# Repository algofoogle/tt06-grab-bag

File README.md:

# Anton's TT06 grab bag

This is a simple analog/mixed-signal project, created from the [TT06 analog template repo](https://github.com/TinyTapeout/tt06-analog-template).

I was invited to participate in the first round of Matt Venn's Zero to ASIC **Analog Course** beta, and this was the design I ultimately submitted to TT06.

It implements:
*   A digital block that generates a few basic 24b-colour (RGB888) VGA test patterns.
*   Analog RGB outputs (running digital block VGA outputs through 3x 8-bit R2R DACs).
*   An extra 4-bit R2R DAC.
*   A bog-standard CMOS inverter. That was my very first custom layout attempt.

**For much more information, [read the full documentation](docs/info.md)**

See [`pcb/`](./pcb/) for PCBs I've been working on related to this.

# What is Tiny Tapeout?

Tiny Tapeout is an educational project that aims to make it easier and cheaper than ever to get your digital designs manufactured on a real chip.

To learn more and get started, visit https://tinytapeout.com.

# Analog projects

For specifications and instructions, see the [analog specs page](https://tinytapeout.com/specs/analog/).

If you have any questions, please join the [Tiny Tapeout Discord](https://tinytapeout.com/discord) and ask in the `#analog` channel.

# Resources

- [FAQ](https://tinytapeout.com/faq/)
- [Digital design lessons](https://tinytapeout.com/digital_design/)
- [Learn how semiconductors work](https://tinytapeout.com/siliwiz/)
- [Join the community](https://tinytapeout.com/discord)

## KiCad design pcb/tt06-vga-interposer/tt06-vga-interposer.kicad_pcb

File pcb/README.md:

# PCB design files for TT06 Grab Bag

*   [`tt06-vga-opamp/`](./tt06-vga-opamp/) is my original prototyping board that I made for testing tt06-grab-bag. I was originally working on it [here](https://github.com/algofoogle/sandpit/tree/master/opamp/tt06-vga-opamp) (private repo).
*   [`tt06-vga-interposer/`](./tt06-vga-interposer/) is a board I'm working on that sits between the TT06 chip carrier board and the TT06 demo board. It taps the analog signals relevant to this design and buffers them with an OPA3355, and includes a VGA socket.

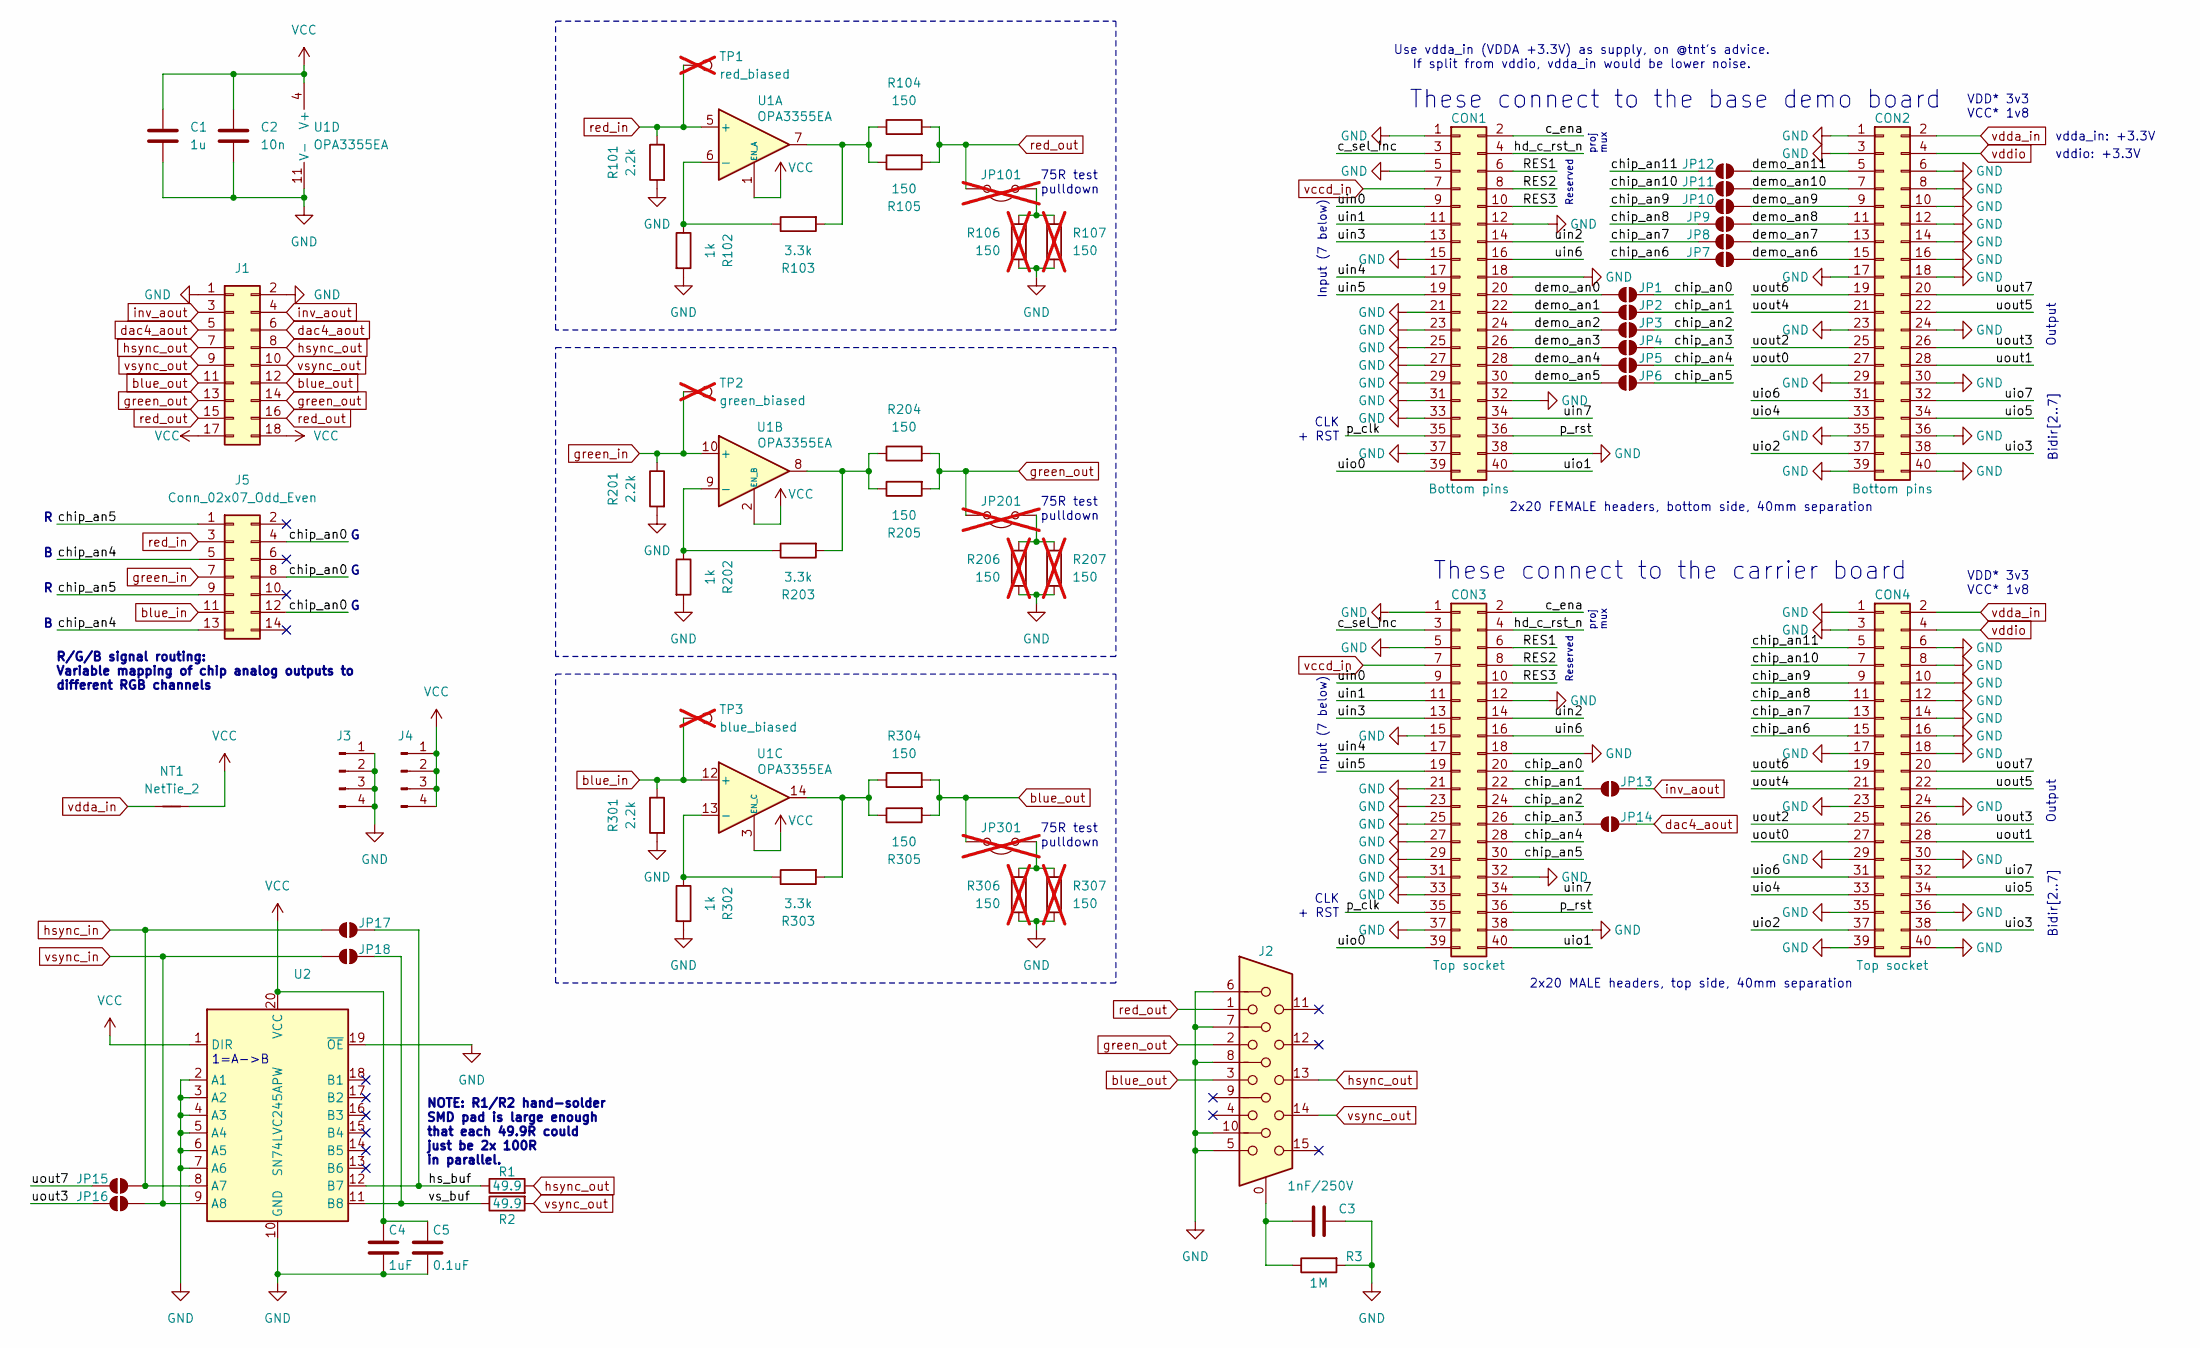
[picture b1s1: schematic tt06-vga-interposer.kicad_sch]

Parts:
C1: 1u; SMD_Passive_HandSolder_0603_to_1210
C2: 10n; SMD_Passive_HandSolder_0603_to_1210
C3: 1nF/250V; SMD_Passive_HandSolder_0603_to_1210
C4: 1uF; SMD_Passive_HandSolder_0603_to_1210
C5: 0.1uF; SMD_Passive_HandSolder_0603_to_1210
CON1, CON2: Bottom pins; PinSocket_2x20_P2.54mm_Vertical; MPN NPTC202KFMS-RC; DigikeyPN S5690-ND
CON3, CON4: Top socket; PinHeader_2x20_P2.54mm_Vertical; MPN NPTC202KFMS-RC; DigikeyPN S5690-ND
J1: Conn_02x09_Odd_Even; PinHeader_2x09_P2.54mm_Vertical
J2: DE15_Receptacle_HighDensity_MountingHoles; DSUB-15-HD_F_Horz_P2.29x2.54mm_EPO3.03mm_MO4.94mm_STRONG
J3, J4: Conn_01x04_Pin; PinHeader_1x04_P2.54mm_Vertical
J5: Conn_02x07_Odd_Even; PinHeader_2x07_P2.54mm_Horizontal
JP1, JP2, JP3, JP4, JP5, JP6, JP7, JP8, JP9, JP10, JP11, JP12, JP13, JP14, JP15, JP16, JP17, JP18: SolderJumper_2_Open; SolderJumper-2_tiny_nomask
JP101, JP201, JP301: Jumper_2_Open; PinHeader_2x01_P2.54mm_Vertical; not fitted
NT1: NetTie_2; NetTie-2_SMD_Pad0.5mm
R1, R2: 49.9; SMD_Passive_HandSolder_0603_to_1210
R3: 1M; SMD_Passive_HandSolder_0603_to_1210
R101, R201, R301: 2.2k; SMD_Passive_HandSolder_0603_to_1210
R102, R202, R302: 1k; SMD_Passive_HandSolder_0603_to_1210
R103, R203, R303: 3.3k; SMD_Passive_HandSolder_0603_to_1210
R104, R105, R204, R205, R304, R305: 150; SMD_Passive_HandSolder_0603_to_1210
R106, R107, R206, R207, R306, R307: 150; SMD_Passive_HandSolder_0603_to_1210; not fitted
TP1: red_biased; PinHeader_1x01_P2.54mm_Vertical; not fitted
TP2: green_biased; PinHeader_1x01_P2.54mm_Vertical; not fitted
TP3: blue_biased; PinHeader_1x01_P2.54mm_Vertical; not fitted
U1: OPA3355EA; TSSOP-14_4.4x5mm_P0.65mm_HandSolder
U2: SN74LVC245APW; TSSOP-20_4.4x6.5mm_P0.65mm_HandSolder

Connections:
/RES1: CON1.6, CON3.6
/RES2: CON1.8, CON3.8
/RES3: CON1.10, CON3.10
/c_ena: CON1.2, CON3.2
/c_sel_inc: CON1.3, CON3.3
/chip_an0: CON3.20, J5.4, J5.8, J5.12, JP1.2 (B)
/chip_an1: CON3.22, JP2.2 (B), JP13.1 (A)
/chip_an2: CON3.24, JP3.2 (B)
/chip_an3: CON3.26, JP4.2 (B), JP14.1 (A)
/chip_an4: CON3.28, J5.5, J5.13, JP5.2 (B)
/chip_an5: CON3.30, J5.1, J5.9, JP6.2 (B)
/chip_an6: CON4.15, JP7.2 (B)
/chip_an7: CON4.13, JP8.2 (B)
/chip_an8: CON4.11, JP9.2 (B)
/chip_an9: CON4.9, JP10.2 (B)
/chip_an10: CON4.7, JP11.2 (B)
/chip_an11: CON4.5, JP12.2 (B)
/demo_an0: CON1.20, JP1.1 (A)
/demo_an1: CON1.22, JP2.1 (A)
/demo_an2: CON1.24, JP3.1 (A)
/demo_an3: CON1.26, JP4.1 (A)
/demo_an4: CON1.28, JP5.1 (A)
/demo_an5: CON1.30, JP6.1 (A)
/demo_an6: CON2.15, JP7.1 (A)
/demo_an7: CON2.13, JP8.1 (A)
/demo_an8: CON2.11, JP9.1 (A)
/demo_an9: CON2.9, JP10.1 (A)
/demo_an10: CON2.7, JP11.1 (A)
/demo_an11: CON2.5, JP12.1 (A)
/hd_c_rst_n: CON1.4, CON3.4
/hs_buf: JP17.2 (B), R1.1, U2.12 (B7)
/p_clk: CON1.35, CON3.35
/p_rst: CON1.36, CON3.36
/uin0: CON1.9, CON3.9
/uin1: CON1.11, CON3.11
/uin2: CON1.14, CON3.14
/uin3: CON1.13, CON3.13
/uin4: CON1.17, CON3.17
/uin5: CON1.19, CON3.19
/uin6: CON1.16, CON3.16
/uin7: CON1.34, CON3.34
/uio0: CON1.39, CON3.39
/uio1: CON1.40, CON3.40
/uio2: CON2.37, CON4.37
/uio3: CON2.38, CON4.38
/uio4: CON2.33, CON4.33
/uio5: CON2.34, CON4.34
/uio6: CON2.31, CON4.31
/uio7: CON2.32, CON4.32
/uout0: CON2.27, CON4.27
/uout1: CON2.28, CON4.28
/uout2: CON2.25, CON4.25
/uout3: CON2.26, CON4.26, JP16.2 (B)
/uout4: CON2.21, CON4.21
/uout5: CON2.22, CON4.22
/uout6: CON2.19, CON4.19
/uout7: CON2.20, CON4.20, JP15.2 (B)
/vs_buf: JP18.2 (B), R2.1, U2.11 (B8)
GND: C1.2, C2.2, C3.2, C4.2, C5.2, CON1.1, CON1.5, CON1.12, CON1.15, CON1.18, CON1.21, CON1.23, CON1.25, CON1.27, CON1.29, CON1.31, CON1.32, CON1.33, CON1.37, CON1.38, CON2.1, CON2.3, CON2.6, CON2.8, CON2.10, CON2.12, CON2.14, CON2.16, CON2.17, CON2.18, CON2.23, CON2.24, CON2.29, CON2.30, CON2.35, CON2.36, CON2.39, CON2.40, CON3.1, CON3.5, CON3.12, CON3.15, CON3.18, CON3.21, CON3.23, CON3.25, CON3.27, CON3.29, CON3.31, CON3.32, CON3.33, CON3.37, CON3.38, CON4.1, CON4.3, CON4.6, CON4.8, CON4.10, CON4.12, CON4.14, CON4.16, CON4.17, CON4.18, CON4.23, CON4.24, CON4.29, CON4.30, CON4.35, CON4.36, CON4.39, CON4.40, J1.1, J1.2, J2.5, J2.6, J2.7, J2.8, J2.10, J3.1, J3.2, J3.3, J3.4, R3.2, R101.2, R102.2, R106.1, R107.1, R201.2, R202.2, R206.1, R207.1, R301.2, R302.2, R306.1, R307.1, U1.11 (V-), U2.2 (A1), U2.3 (A2), U2.4 (A3), U2.5 (A4), U2.6 (A5), U2.7 (A6), U2.10 (GND), U2.19 (~OE)
unnamed: C3.1, J2.0, R3.1
unnamed: JP101.2 (B), R106.2, R107.2
unnamed: JP201.2 (B), R206.2, R207.2
unnamed: JP301.2 (B), R306.2, R307.2
unnamed: R103.2, R104.1, R105.1, U1.7
unnamed: R203.2, R204.1, R205.1, U1.8
unnamed: R303.2, R304.1, R305.1, U1.14
unnamed: R102.1, R103.1, U1.6 (-)
unnamed: R202.1, R203.1, U1.9 (-)
unnamed: R302.1, R303.1, U1.13 (-)
VCC: C1.1, C2.1, C4.1, C5.1, J1.17, J1.18, J4.1, J4.2, J4.3, J4.4, NT1.1, U1.1 (EN_A), U1.2 (EN_B), U1.3 (EN_C), U1.4 (V+), U2.1 (DIR), U2.20 (VCC)
blue_in: J5.11, R301.1, TP3.1, U1.12 (+)
blue_out: J1.11, J1.12, J2.3, JP301.1 (A), R304.2, R305.2
dac4_aout: J1.5, J1.6, JP14.2 (B)
green_in: J5.7, R201.1, TP2.1, U1.10 (+)
green_out: J1.13, J1.14, J2.2, JP201.1 (A), R204.2, R205.2
hsync_in: JP15.1 (A), JP17.1 (A), U2.8 (A7)
hsync_out: J1.7, J1.8, J2.13, R1.2
inv_aout: J1.3, J1.4, JP13.2 (B)
red_in: J5.3, R101.1, TP1.1, U1.5 (+)
red_out: J1.15, J1.16, J2.1, JP101.1 (A), R104.2, R105.2
vccd_in: CON1.7, CON3.7
vdda_in: CON2.2, CON4.2, NT1.2
vddio: CON2.4, CON4.4
vsync_in: JP16.1 (A), JP18.1 (A), U2.9 (A8)
vsync_out: J1.9, J1.10, J2.14, R2.2

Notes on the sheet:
Output
proj mux
Use vdda_in (VDDA +3.3V) as supply, on @tnt's advice. If split from vddio, vdda_in would be lower noise.
VDD* 3v3 VCC* 1v8
vdda_in: +3.3V
Reserved
75R test pulldown
These connect to the carrier board
2x20 FEMALE headers, bottom side, 40mm separation
Input (7 below)
2x20 MALE headers, top side, 40mm separation
vddio: +3.3V
R/G/B signal routing: Variable mapping of chip analog outputs to different RGB channels
NOTE: R1/R2 hand-solder SMD pad is large enough that each 49.9R could just be 2x 100R in parallel.
Bidir[2..7]
These connect to the base demo board
1=A->B
CLK + RST

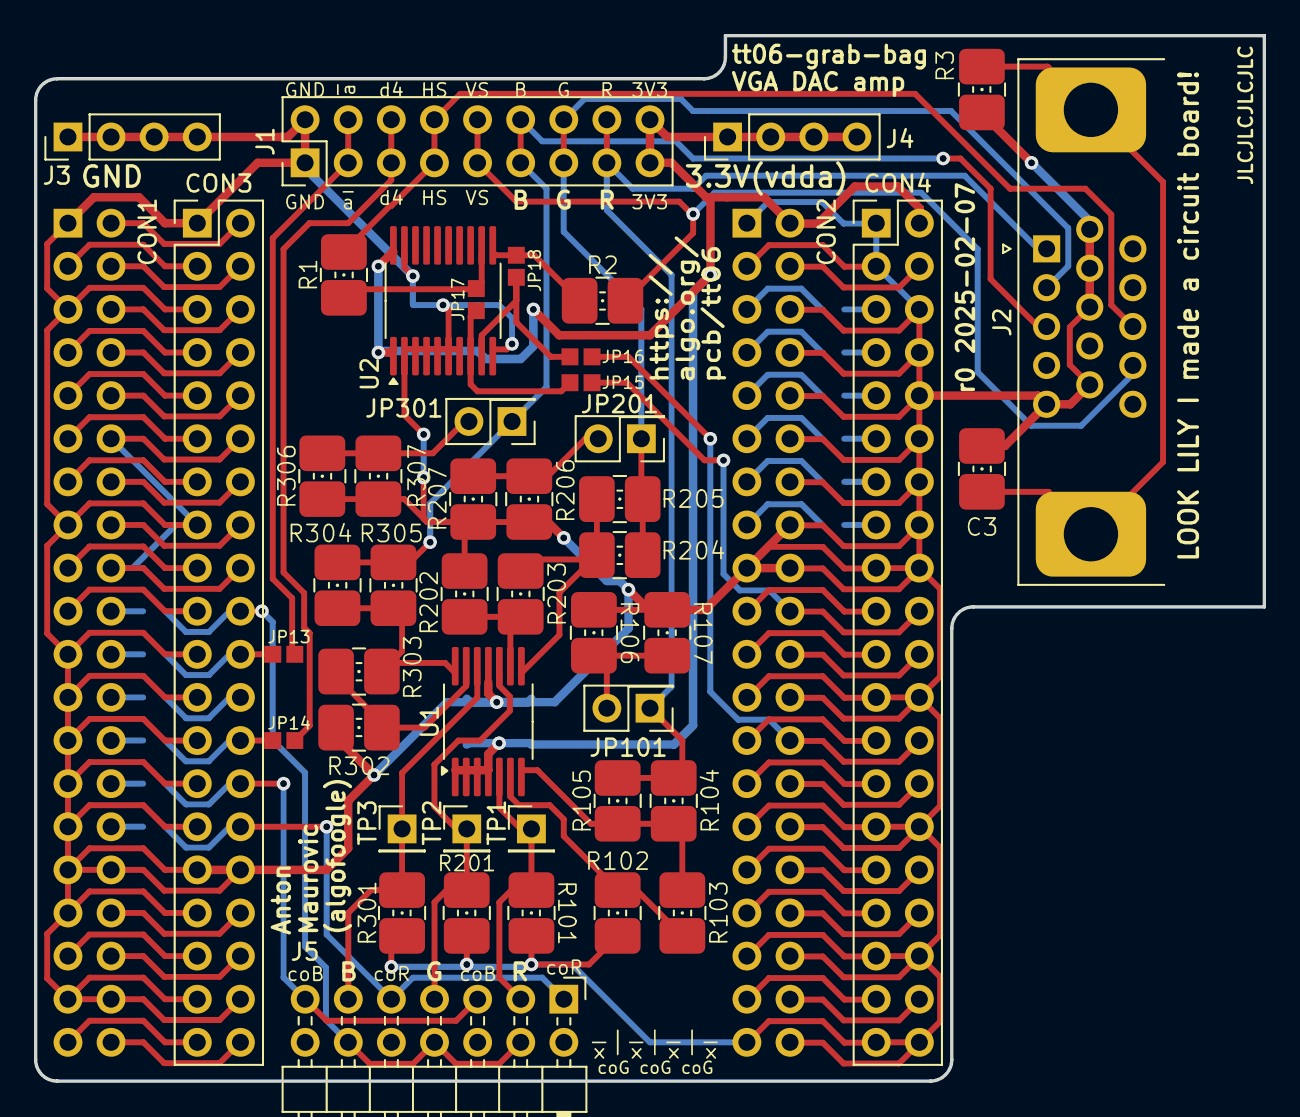
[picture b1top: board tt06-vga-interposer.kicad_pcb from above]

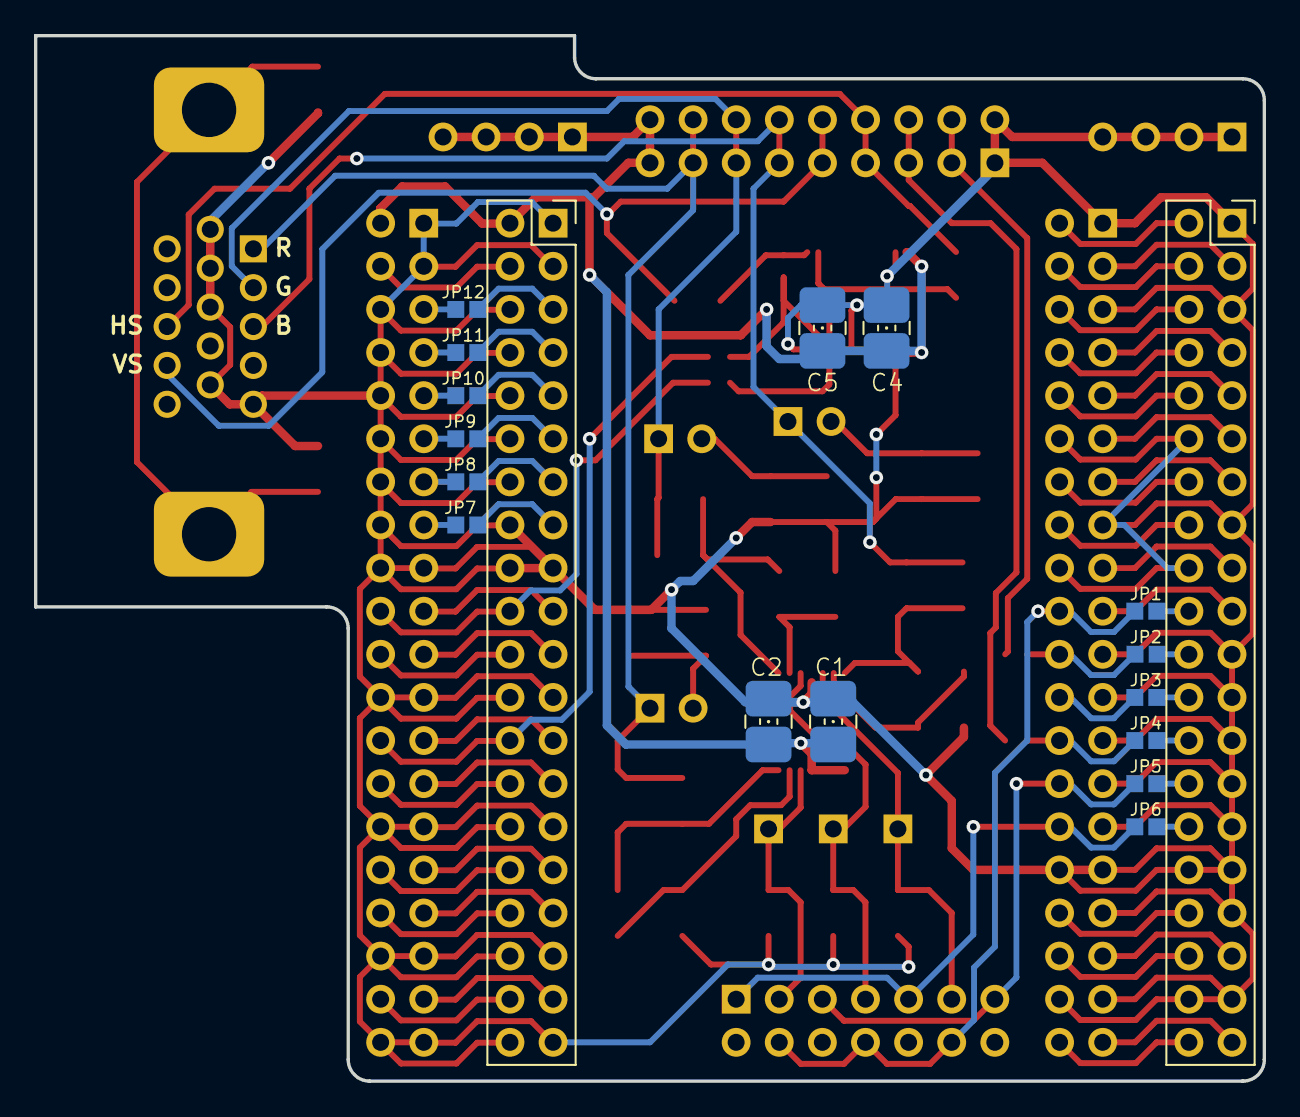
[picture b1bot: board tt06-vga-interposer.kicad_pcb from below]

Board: 2 copper layers, 72.4 x 61.6 mm, 65 parts (18 on the bottom side), 85 nets.

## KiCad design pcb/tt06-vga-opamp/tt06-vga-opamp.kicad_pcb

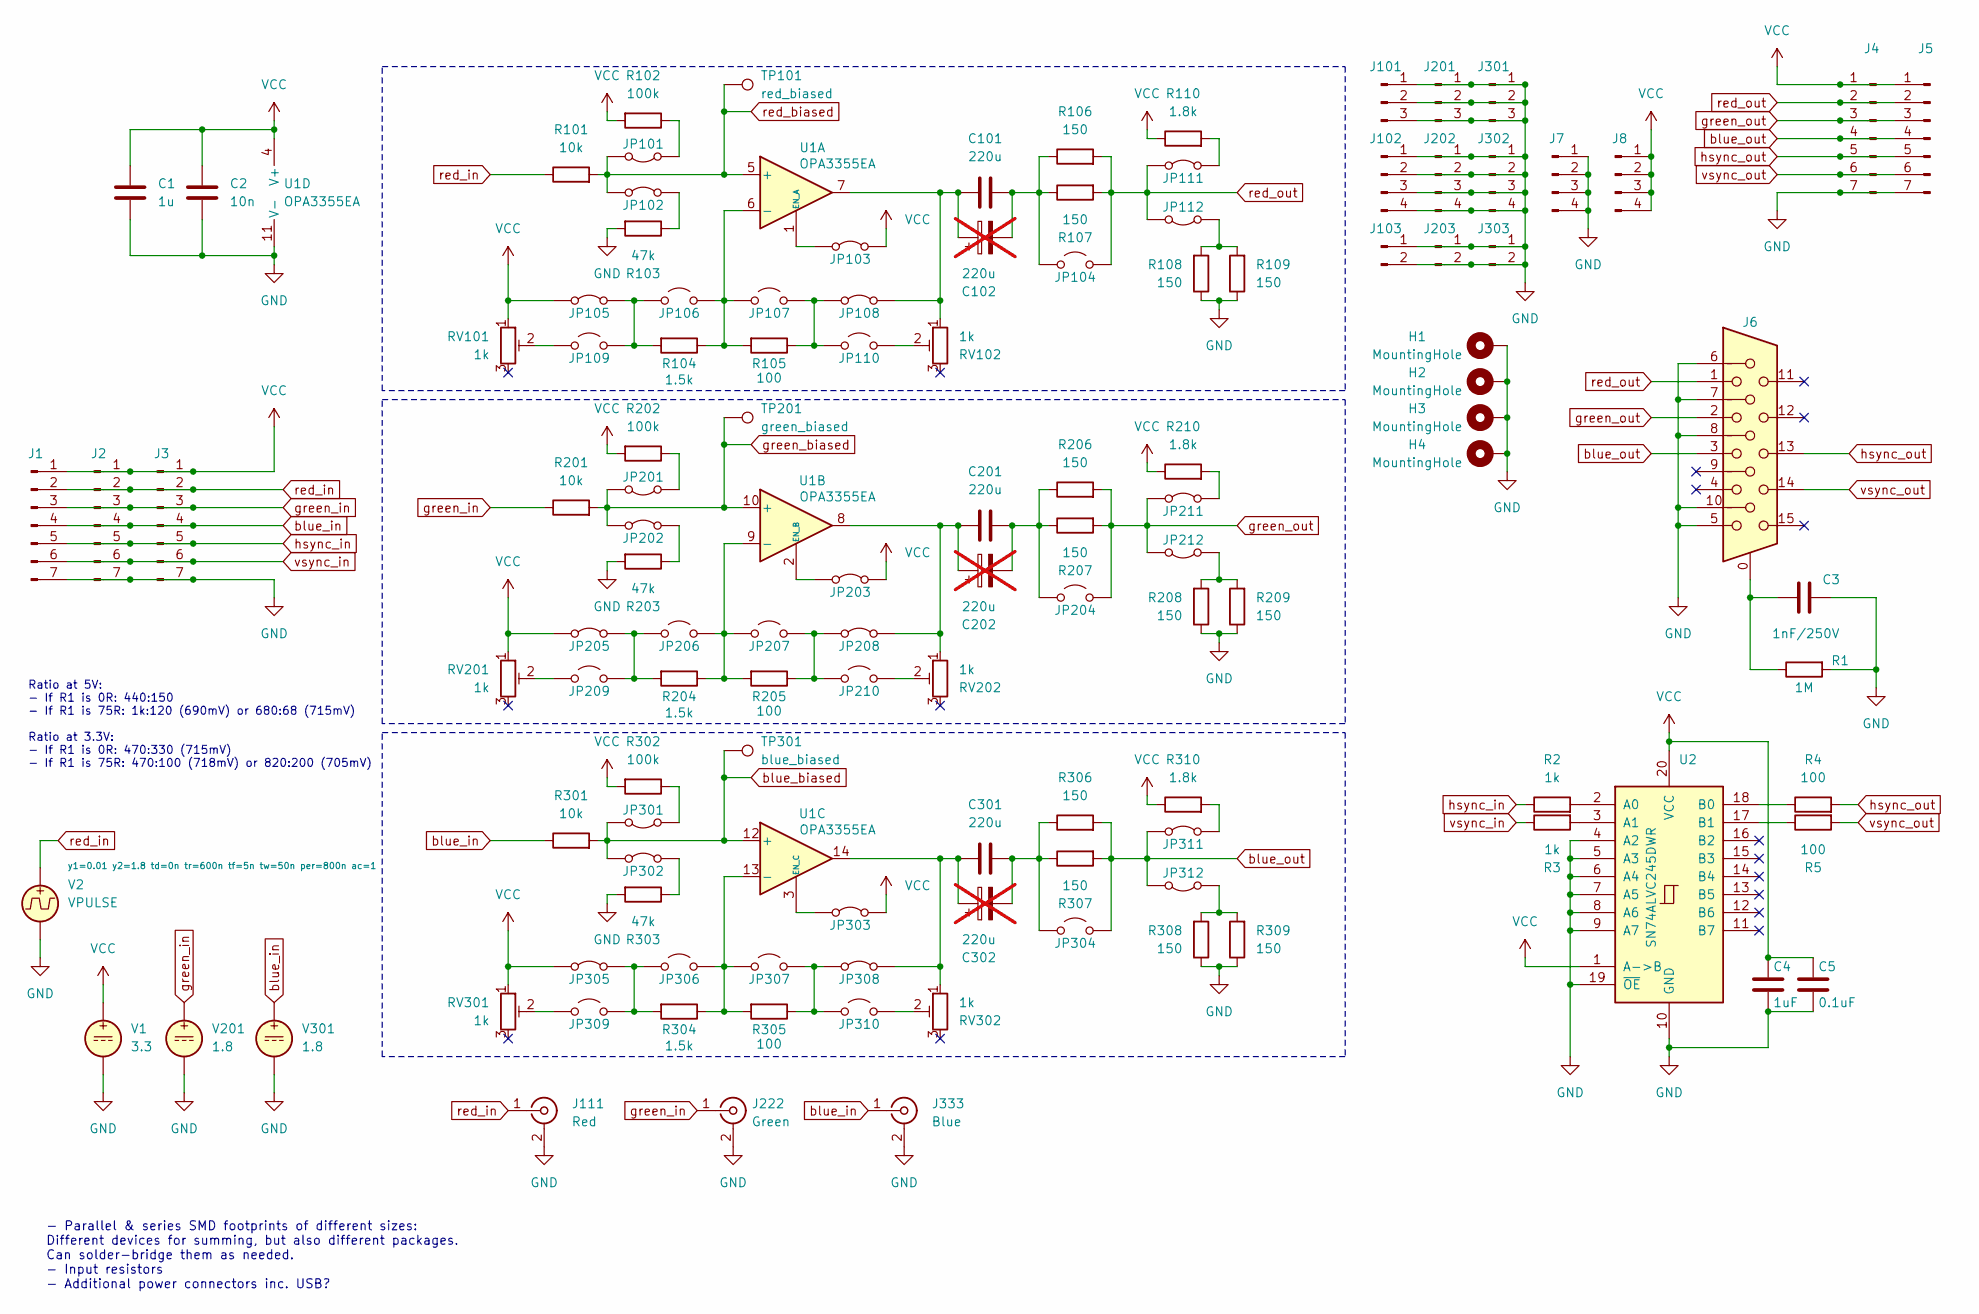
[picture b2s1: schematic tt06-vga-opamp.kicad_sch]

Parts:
C1: 1u; SMD_Passive_HandSolder_0603_to_1210
C2: 10n; SMD_Passive_HandSolder_0603_to_1210
C3: 1nF/250V; SMD_Passive_HandSolder_0603_to_1210
C4: 1uF; SMD_Passive_HandSolder_0603_to_1210
C5: 0.1uF; SMD_Passive_HandSolder_0603_to_1210
C101, C201, C301: 220u; SMD_Passive_HandSolder_0603_to_1210
C102, C202, C302: 220u; CP_Radial_D10.0mm_P2.50mm_P5.00mm; not fitted
H1, H2, H3, H4: MountingHole; MountingHole_4.3mm_M4_DIN965_Pad
J1, J2, J3, J4, J5: Conn_01x07_Pin; PinHeader_1x07_P2.54mm_Vertical
J6: DE15_Receptacle_HighDensity_MountingHoles; DSUB-15-HD_F_Horz_P2.29x2.54mm_EPO3.03mm_MO4.94mm_STRONG
J7, J8, J102, J202, J302: Conn_01x04_Pin; PinHeader_1x04_P2.54mm_Vertical
J101, J201, J301: Conn_01x03_Pin; PinHeader_1x03_P2.54mm_Vertical
J103, J203, J303: Conn_01x02_Pin; PinHeader_1x02_P2.54mm_Vertical
J111: Red; LINX_CONMHF1-SMD-G-T_U.FL_HandSolder
J222: Green; LINX_CONMHF1-SMD-G-T_U.FL_HandSolder
J333: Blue; LINX_CONMHF1-SMD-G-T_U.FL_HandSolder
JP101, JP102, JP103, JP105, JP108, JP111, JP112, JP201, JP202, JP203, JP205, JP208, JP211, JP212, JP301, JP302, JP303, JP305, JP308, JP311, JP312: Jumper_2_Bridged; PinHeader_1x02_P2.54mm_Vertical
JP104, JP106, JP107, JP109, JP110, JP204, JP206, JP207, JP209, JP210, JP304, JP306, JP307, JP309, JP310: Jumper_2_Open; PinHeader_1x02_P2.54mm_Vertical
R1: 1M; SMD_Passive_HandSolder_0603_to_1210
R2, R3: 1k; SMD_Passive_HandSolder_0603_to_1210
R4, R5, R105, R205, R305: 100; SMD_Passive_HandSolder_0603_to_1210
R101, R201, R301: 10k; SMD_Passive_HandSolder_0603_to_1210
R102, R202, R302: 100k; SMD_Passive_HandSolder_0603_to_1210
R103, R203, R303: 47k; SMD_Passive_HandSolder_0603_to_1210
R104, R204, R304: 1.5k; SMD_Passive_HandSolder_0603_to_1210
R106, R107, R108, R109, R206, R207, R208, R209, R306, R307, R308, R309: 150; SMD_Passive_HandSolder_0603_to_1210
R110, R210, R310: 1.8k; SMD_Passive_HandSolder_0603_to_1210
RV101, RV102, RV201, RV202, RV301, RV302: 1k; Potentiometer_Runtron_RM-065_Vertical
TP101: red_biased; PinHeader_1x01_P2.54mm_Vertical
TP201: green_biased; PinHeader_1x01_P2.54mm_Vertical
TP301: blue_biased; PinHeader_1x01_P2.54mm_Vertical
U1: OPA3355EA; TSSOP-14_4.4x5mm_P0.65mm_HandSolder
U2: SN74ALVC245DWR; SOIC-20W_7.5x12.8mm_P1.27mm
V1: 3.3
V2: VPULSE
V201, V301: 1.8

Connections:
GND: C1.2, C2.2, C3.2, C4.2, C5.2, H1.1, H2.1, H3.1, H4.1, J1.7, J2.7, J3.7, J4.7, J5.7, J6.5, J6.6, J6.7, J6.8, J6.10, J7.1, J7.2, J7.3, J7.4, J101.1, J101.2, J101.3, J102.1, J102.2, J102.3, J102.4, J103.1, J103.2, J111.2 (Ext), J201.1, J201.2, J201.3, J202.1, J202.2, J202.3, J202.4, J203.1, J203.2, J222.2 (Ext), J301.1, J301.2, J301.3, J302.1, J302.2, J302.3, J302.4, J303.1, J303.2, J333.2 (Ext), R1.2, R103.2, R108.1, R109.1, R203.2, R208.1, R209.1, R303.2, R308.1, R309.1, U1.11 (V-), U2.4 (A2), U2.5 (A3), U2.6 (A4), U2.7 (A5), U2.8 (A6), U2.9 (A7), U2.10 (GND), U2.19 (~OE), V1.2, V2.2, V201.2, V301.2
unnamed: C3.1, J6.0, R1.1
unnamed: JP101.2 (B), R102.1
unnamed: JP102.2 (B), R103.1
unnamed: JP103.1 (A), U1.1 (EN_A)
unnamed: C101.2, C102.2, JP104.1 (A), R106.1, R107.1
unnamed: JP105.2 (B), JP106.1 (A), JP109.2 (B), R104.2
unnamed: JP106.2 (B), JP107.1 (A), R104.1, R105.2, U1.6 (-)
unnamed: JP107.2 (B), JP108.1 (A), JP110.1 (A), R105.1
unnamed: C101.1, C102.1, JP108.2 (B), RV102.1, U1.7
unnamed: JP109.1 (A), RV101.2
unnamed: JP110.2 (B), RV102.2
unnamed: JP111.2 (B), R110.2
unnamed: JP112.1 (A), R108.2, R109.2
unnamed: JP201.2 (B), R202.1
unnamed: JP202.2 (B), R203.1
unnamed: JP203.1 (A), U1.2 (EN_B)
unnamed: C201.2, C202.2, JP204.1 (A), R206.1, R207.1
unnamed: JP205.2 (B), JP206.1 (A), JP209.2 (B), R204.2
unnamed: JP206.2 (B), JP207.1 (A), R204.1, R205.2, U1.9 (-)
unnamed: JP207.2 (B), JP208.1 (A), JP210.1 (A), R205.1
unnamed: C201.1, C202.1, JP208.2 (B), RV202.1, U1.8
unnamed: JP209.1 (A), RV201.2
unnamed: JP210.2 (B), RV202.2
unnamed: JP211.2 (B), R210.2
unnamed: JP212.1 (A), R208.2, R209.2
unnamed: JP301.2 (B), R302.1
unnamed: JP302.2 (B), R303.1
unnamed: JP303.1 (A), U1.3 (EN_C)
unnamed: C301.2, C302.2, JP304.1 (A), R306.1, R307.1
unnamed: JP305.2 (B), JP306.1 (A), JP309.2 (B), R304.2
unnamed: JP306.2 (B), JP307.1 (A), R304.1, R305.2, U1.13 (-)
unnamed: JP307.2 (B), JP308.1 (A), JP310.1 (A), R305.1
unnamed: C301.1, C302.1, JP308.2 (B), RV302.1, U1.14
unnamed: JP309.1 (A), RV301.2
unnamed: JP310.2 (B), RV302.2
unnamed: JP311.2 (B), R310.2
unnamed: JP312.1 (A), R308.2, R309.2
unnamed: R2.2, U2.2 (A0)
unnamed: R3.2, U2.3 (A1)
unnamed: R4.1, U2.18 (B0)
unnamed: R5.1, U2.17 (B1)
VCC: C1.1, C2.1, C4.1, C5.1, J1.1, J2.1, J3.1, J4.1, J5.1, J8.1, J8.2, J8.3, J8.4, JP103.2 (B), JP105.1 (A), JP203.2 (B), JP205.1 (A), JP303.2 (B), JP305.1 (A), R102.2, R110.1, R202.2, R210.1, R302.2, R310.1, RV101.1, RV201.1, RV301.1, U1.4 (V+), U2.1 (A->B), U2.20 (VCC), V1.1
blue_biased: JP301.1 (A), JP302.1 (A), R301.2, TP301.1, U1.12 (+)
blue_in: J1.4, J2.4, J3.4, J333.1 (In), R301.1, V301.1
blue_out: J4.4, J5.4, J6.3, JP304.2 (B), JP311.1 (A), JP312.2 (B), R306.2, R307.2
green_biased: JP201.1 (A), JP202.1 (A), R201.2, TP201.1, U1.10 (+)
green_in: J1.3, J2.3, J3.3, J222.1 (In), R201.1, V201.1
green_out: J4.3, J5.3, J6.2, JP204.2 (B), JP211.1 (A), JP212.2 (B), R206.2, R207.2
hsync_in: J1.5, J2.5, J3.5, R2.1
hsync_out: J4.5, J5.5, J6.13, R4.2
red_biased: JP101.1 (A), JP102.1 (A), R101.2, TP101.1, U1.5 (+)
red_in: J1.2, J2.2, J3.2, J111.1 (In), R101.1, V2.1
red_out: J4.2, J5.2, J6.1, JP104.2 (B), JP111.1 (A), JP112.2 (B), R106.2, R107.2
vsync_in: J1.6, J2.6, J3.6, R3.1
vsync_out: J4.6, J5.6, J6.14, R5.2

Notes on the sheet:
- Parallel & series SMD footprints of different sizes: Different devices for summing, but also different packages. Can solder-bridge them as needed. - Input resistors - Additional power connectors inc. USB?
Ratio at 5V: - If R1 is 0R: 440:150 - If R1 is 75R: 1k:120 (690mV) or 680:68 (715mV) Ratio at 3.3V: - If R1 is 0R: 470:330 (715mV) - If R1 is 75R: 470:100 (718mV) or 820:200 (705mV)

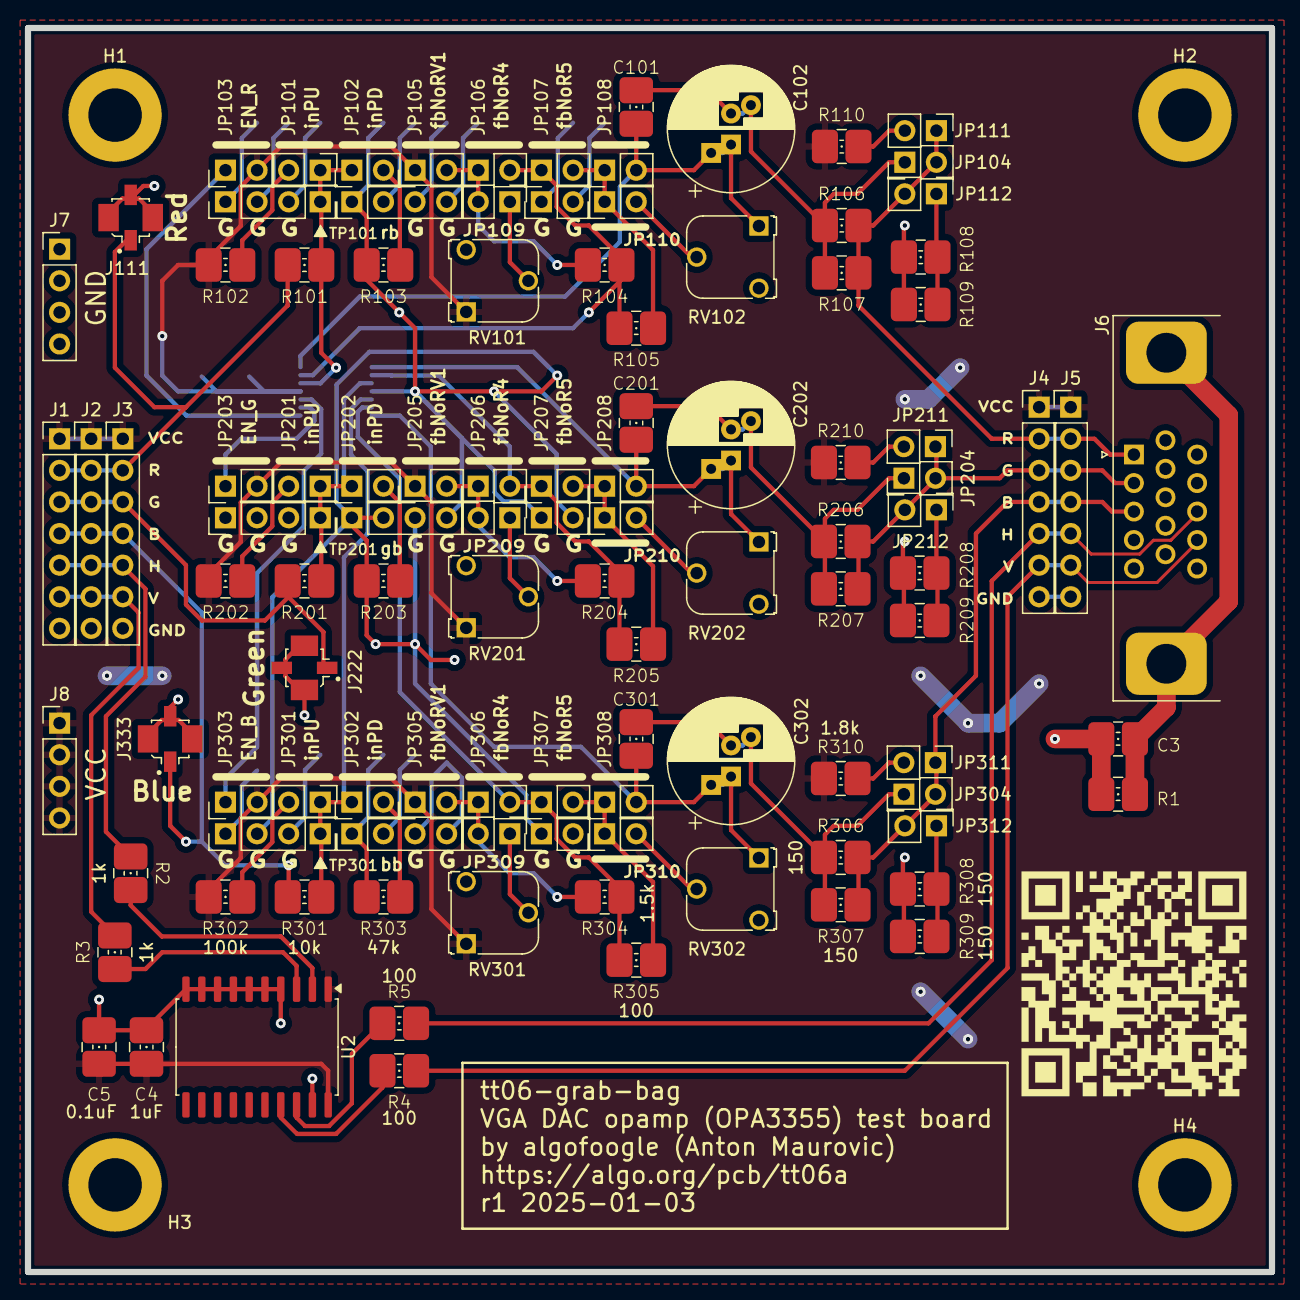
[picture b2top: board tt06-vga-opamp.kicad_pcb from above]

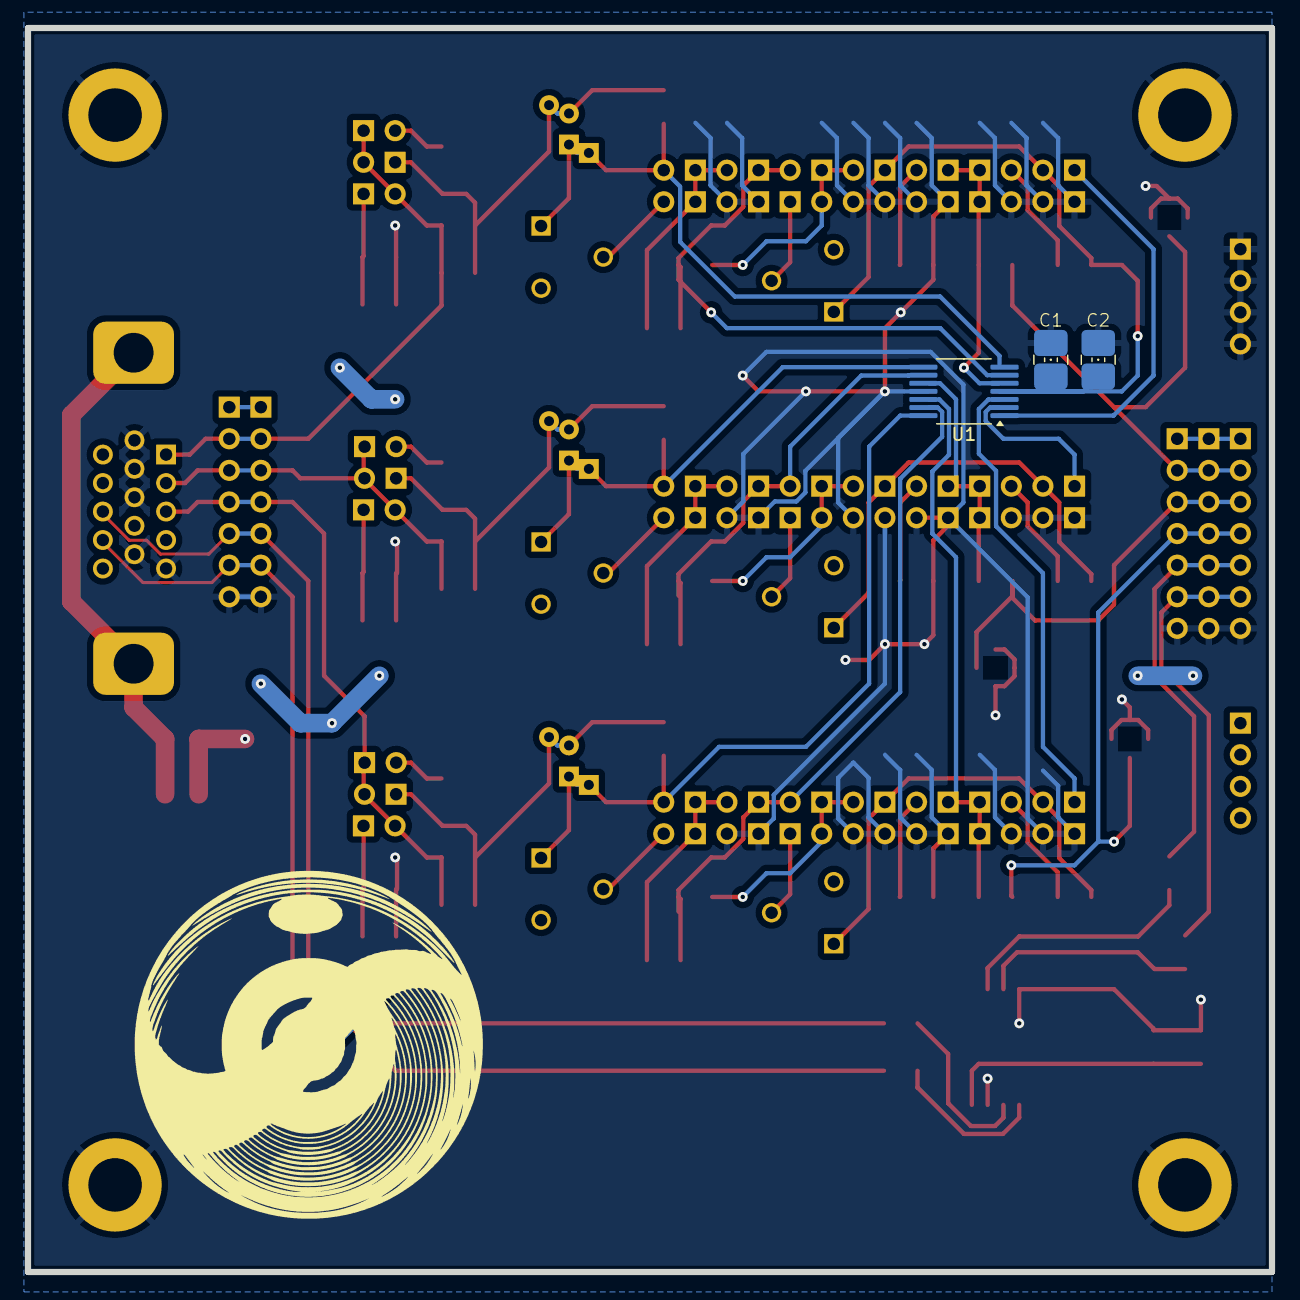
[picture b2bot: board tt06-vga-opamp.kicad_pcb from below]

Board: 2 copper layers, 100.0 x 100.0 mm, 117 parts (3 on the bottom side), 56 nets.

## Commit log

2024-04-03 Basic inverter schematic and symbol in xschem
2024-04-03 Adding basic testbench for inverter
2024-04-03 Inverter testbench: Add Tiny Tapeout analog output load
2024-04-03 Inverter 4x size; current graph in TB
2024-04-04 Change tb_inverter to Monte Carlo sim
2024-04-04 Adding Magic layout for inverter cell
2024-04-09 LVS works for inverter. Inverter parax sim added to tb_inverter
2024-04-09 Inverted PNR in TT wrapper
2024-04-09 Verilog updated
2024-04-10 Tie unused outputs to VGND; LVS failing tho
2024-04-11 Fix LVS
2024-04-11 Generated GDS/LEF and updated info.yaml
2024-04-11 Minor doco update
2024-04-12 Progress on R2R DAC, and fix for integration DRC error. See: https://discord.com/channels/1009193568256135208/1162428058817540116/1228303318309142610
2024-04-17 Layout done for R2R DAC
2024-04-17 Change R2R to not use bus names for ports
2024-04-17 Put PEX into tb_r2r
2024-04-17 Integrate R2R DAC into TT template
2024-04-18 Quick test with a single resistor
2024-04-18 Working on Verilog block for VGA controller
2024-04-18 Successful harden of controller block
2024-04-19 Wiring up controller and 3 DACs in top module. Pinout changed
2024-04-19 Progress on layout with controller, but needs to be rehardened
2024-04-19 Modified and rehardened controller; progress on wiring it all up
2024-04-19 More progress on wiring
2024-04-19 Continuing wiring progress
2024-04-19 All wired up, I think
2024-04-19 Update LVS script
2024-04-19 Minor corrections, LVS clean, GDS generated!
2024-04-19 Trying to fix KLayout FEOL DRC by using readonly GDS placement instead of mag
2024-04-19 More DRC fixing
2024-04-19 More DRC messing around
2024-04-19 About to try controller MAG made from clean readonly GDS
2024-04-19 Tried controller place again. Let's see [no ci]
2024-04-19 make update_gds worked better this time. KLayout can view this GDS
2024-04-19 Adding r2r_extra: just 4 bits connected to uio_in[6:3]
2024-04-29 Simple voltage buffer PFET
2024-05-01 j_opamp kinda works
2024-05-01 Really primitive raw=>ppm python script
2024-05-04 Trying to get ngspice cosimulation (mixed signal) to work
2024-05-04 Tidy up cosim, plots, and create sim/Makefile
2024-05-04 tt07-hacking: Just dump in some old opamp test stuff
2024-05-06 Working on improved output rendering
2024-05-06 Trying out NFET as current source
2024-05-06 Can now render various modes as screen images
2024-05-07 Abstracting DAC output boost as 'dacboost' subcircuit
2024-05-08 Better sim/render control and more output quality tests
2024-05-09 Tidying some stuff up for sim and render
2024-05-09 Minor update
2024-05-10 Updating doco
2024-05-10 Minor update for GFM (hopefully fine for PDF doc also)
2024-05-10 Minor correction again
2024-05-10 Oops, forgot the actual fix
2024-05-10 C'mon!
2025-01-28 Adding PCB design stuff
2025-01-30 Partial layout of interposer PCB
2025-02-03 Nearly finished 1st draft of interposer PCB
2025-02-07 Interposer PCB: First complete version
2025-02-07 Interposer PCB: Rounded corners
2025-02-08 Interposer PCB: Thicken power traces, add final Gerbers
2025-02-20 Minor updates
2025-02-20 Fix sim for 40ns pixel time; add digital in graph
2025-02-20 Tweak a few other parts of the sim and docs
2025-02-22 Add digital controller block's original OpenLane hardening results
2025-02-23 Tidy up interposer schematic a little
2025-02-23 Update docs a bit more re testing results
2025-02-23 Fix for docs generation
2025-02-23 Trying a docs image fix
2025-02-23 Doc headings fix
2025-02-23 Another doc fix
2025-02-23 Clean up the fixed docs
2025-05-01 Fix PCB library path [no ci]
